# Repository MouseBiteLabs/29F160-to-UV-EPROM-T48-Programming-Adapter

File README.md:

# TSOP NOR Flash Programming Adapter for T48

This is an untested programming adapter for the T48 for programming already-soldered 29F160 chips on my <a href="https://github.com/MouseBiteLabs/ROM-Adapter-Boards/tree/main/29F160%20to%20UV%20EPROM">29F160 to UV EPROM Adapter board.</a> This *should* make it easy to reprogram the one or two flash chips on the adapters without having to desolder anything. I have not tested this yet, so consider this *experimental*. I will, of course, update the repo accordingly if my testing proves successful.

All gerbers and source files can be found in this repo, as this project is fully open source. Please read all instructions associated with this board before assembling.

## Board Characteristics and Order Information

The zipped folder contains all the gerber files for this board. You can generally choose whatever thickness you want, but I usually stick to at least 1.0mm.

You can order this board on OSH Park here: https://oshpark.com/shared_projects/9QicVnyQ

Alternatively, you can use the zipped folder at any board fabricator you like. You may also buy the board from PCBWay using this link (NOT YET AVAILABLE) (disclosure: I receive 10% of the sale value to go towards future PCB orders of my own):

## Required Equipment

- You will need basic tools, like a soldering iron.
- You'll need an extra 2x8 2.54mm female-female IDC ribbon cable, like this one: https://www.digikey.com/short/b1q09p80
  - Alternatively, you can use DuPont breadboard female-female jumpers, like these: https://www.digikey.com/short/vm5d3m4h
- This programming adapter requires the <a href="https://xgecu.myshopify.com/products/100-original-xgecu-adp_f48_ex-1-tsop48-special-adapter-for-nor-flash-only-use-on-t48-tl866-3g-programmer">T48's XGecu TSOP adapter board</a> to be placed on the right socket (P1). This is because it has a proprietary EEPROM (U1) that communicates with the T48.
  - If you want, you can transfer over this EEPROM to *this* adapter board, along with R1 and C1 (a 4.7k resistor and 0.1uF capacitor); or you could simply piggy-back the TSOP adapter on P1, connect the ISP cable from J2 to the TSOP adapter, and keep the TSOP socket unused.

## Supported Boards

P2 accepts the v2.0 version of the 29F160 to UV EPROM adapter boards. It does not support previous revisions.

## How to Assemble and Use the Adapter

### Step 1: Assembly

- You will likely want to populate the right side of each row of pins first with male header pins (2.54mm), which need to have the longer sides sticking down below the board. This will be the rows of pins that go into the T48 programmer. Then, populate the left side of each row of pins with female header pins (2.54mm). This will be where the XGecu TSOP Adapter is housed. 

It's much easier to assemble it in this way, as you can see here:

(Alternatively, you can use only one set of these pins with female socket headers that have longer pins so that you can place it in the T48 *and* connect the XGecu Adapter.)

- P2 and the /BYTE, /RP, and /WE pins (the ones located inside the P2 footprint) are populated with simple female header sockets (2.54mm).

- J1 and J2 are populated with simple male header pins (2.54mm).

- SW1 and SW2 are SPDT switches: https://www.digikey.com/short/zvmm2dj3

- U1, R1, and C1 are discussed below. They are not required for operation, but may be harvested from the XGecu TSOP Adapter.

### Step 2: Connect XGecu TSOP Adapter and 29F160 to UV EPROM Board

With the programming adapter placed in the T48 (check polarity!), place the XGecu TSOP adapter into P1 on the left in the correct orientation. Then, connect one IDC cable from the T48's 16-pin socket to J1 (again, mind the polarity). Connect a second IDC cable from J2 to the XGecu TSOP adapter.

Finally, place the 29F160 to UV EPROM board in the left socket P2.

[TO DO: pic]

### Step 3: Configure the Switches

SW1 and SW2 are for correctly configuring the 29F160 UV EPROM board for programming.

If you are using just one 29F160 chip, place SW2 in the "1x NOR" setting. If you are using two, then place SW2 in the "2x NOR" setting.

When programming a 2x 29F160 board, your ROM files must be in 2MB (16Mbit) chunks. To program the first 29F160 with the first 2MB chunk, place SW1 in the "1ST" setting. To program the second, switch SW1 to the "2ND" setting. If you are only using 1x 29F160, this switch does nothing.

## Bill of Materials (BOM)

As far as the headers (male and female) go, there are plenty of places to get them from at better prices. I personally have drawers full of them, so I didn't need to buy any extra. But if you're looking for exact parts, you can use these. The only parts you may need to buy, if you have a stock of headers and jumper cables ready to go, are the EG1271 switches.

Please note that P1 has two different options, and Option A is a set of 2 separate part numbers (this is the option shown in pictures above in the assembly section with separate male and female headers). P2 has three separate part numbers to populate all of the pins with female sockets while being cost effective.

Also note that in breaking with tradition from my other repositories, I have *Digikey* links listed. This is simply because Mouser did not have an equivalent IDC cable that didn't cost like $10. You can find all the other parts on this list at Mouser as well.

| Reference     | Qty | Value/Part Number | Package                                   | Description                     | Source                                                                           |
| ------------- | --- | ----------------- | ----------------------------------------- | ------------------------------- | -------------------------------------------------------------------------------- |
| Cable (Opt A) | 1   | H3CCH-1606G       | 2x8, 0.1" Spacing                         | IDC Cable                       | [https://www.digikey.com/short/j5rt9349](https://www.digikey.com/short/j5rt9349) |
| Cable (Opt B) | 1   | 1950              | \-                                        | Jumper Wire F-to-F              | [https://www.digikey.com/short/5wr7q7fz](https://www.digikey.com/short/5wr7q7fz) |
| J1, J2        | 2   | 77313-818-16LF    | 2x8, 0.1" Spacing                         | 16 Position Header Pins, Male   | [https://www.digikey.com/short/13fhc19n](https://www.digikey.com/short/13fhc19n) |
| SW1, SW2      | 2   | EG1271            | 2x3 Pins                                  | SPDT Slide Switch               | [https://www.digikey.com/short/vj8nm90f](https://www.digikey.com/short/vj8nm90f) |
| P1 (Opt A)    | 2   | PPPC201LFBN-RC    | 20 Pins, 0.1" Spacing                     | 20 Position Header Pins, Female | [https://www.digikey.com/short/7rdtqfvp](https://www.digikey.com/short/7rdtqfvp) |
|               | 2   | PRPC020SAAN-RC    | 20 Pins, 0.1" Spacing                     | 20 Position Header Pins, Male   | [https://www.digikey.com/short/zpzj5p9h](https://www.digikey.com/short/zpzj5p9h) |
| P1 (Opt B)    | 4   | SSQ-110-03-G-S    | 10 Pins, 0.1" Spacing, 0.394" Post Length | 10 Position Header Pins, Female | [https://www.digikey.com/short/rvwzhn13](https://www.digikey.com/short/rvwzhn13) |
| P2            | 2   | PPPC201LFBN-RC    | 20 Pins, 0.1" Spacing                     | 20 Position Header Pins, Female | [https://www.digikey.com/short/7rdtqfvp](https://www.digikey.com/short/7rdtqfvp) |
|               | 1   | PPPC021LFBN-RC    | 2 Pins, 0.1" Spacing                      | 2 Position Header Pins, Female  | [https://www.digikey.com/short/bd5t98qm](https://www.digikey.com/short/bd5t98qm) |
|               | 1   | PPPC031LFBN-RC    | 3 Pins, 0.1" Spacing                      | 3 Position Header Pins, Female  | [https://www.digikey.com/short/p04ft8t8](https://www.digikey.com/short/p04ft8t8) |

## What's with U1, R1, and C1?

On the XGecu TSOP Programming Adapter, these 3 components are included. This is a proprietary EEPROM for communicating with the T48. I believe this is a form of copy protection. If you wish, you can transfer these components over to this board instead - this would remove the need of placing the XGecu adapter into P1. *(Maybe a clever person could reverse engineer the EEPROM by sniffing pins 5 and 6, which are the only two pins used on this chip)*

## What's with the P37/VCC and P29/GND/P18 Pins?

This is basically for helping me troubleshoot if I run into problems. One of the things I'm unsure of is if the T48 will throw an error if it detects the larger-than-normal load due to the extra circuitry on my TSOP adapter boards. 

Pin 37 on the T48 is connected to the VCC pin of the TSOP chip, but it is not directly connected to VCC itself, which is pin 14 of J1/J2. The jumper is there in case the TSOP board current limits the programmer with the extra circuitry on it. Though, that might cause other problems, so it is not hard-wired. Pin 18 and pin 29 are a similar case for VSS.

You can ignore these pins (unless I update the repo further to address them).

## Revision History

### v1.1 - Prototype II

- Disconnected pin 18 and pin 29 on P1 from VSS and connect to the proper pins on P2 instead
- Renamed board to be more general
- Added more pins for ZIF socket access

### v1.0 - Prototype

## License

<br />This work is licensed under a <a rel="license" href="http://creativecommons.org/licenses/by-sa/4.0/">Creative Commons Attribution-ShareAlike 4.0 International License</a>. You are able to copy and redistribute the material in any medium or format, as well as remix, transform, or build upon the material for any purpose (even commercial) - but you **must** give appropriate credit, provide a link to the license, and indicate if any changes were made.

©MouseBiteLabs 2025

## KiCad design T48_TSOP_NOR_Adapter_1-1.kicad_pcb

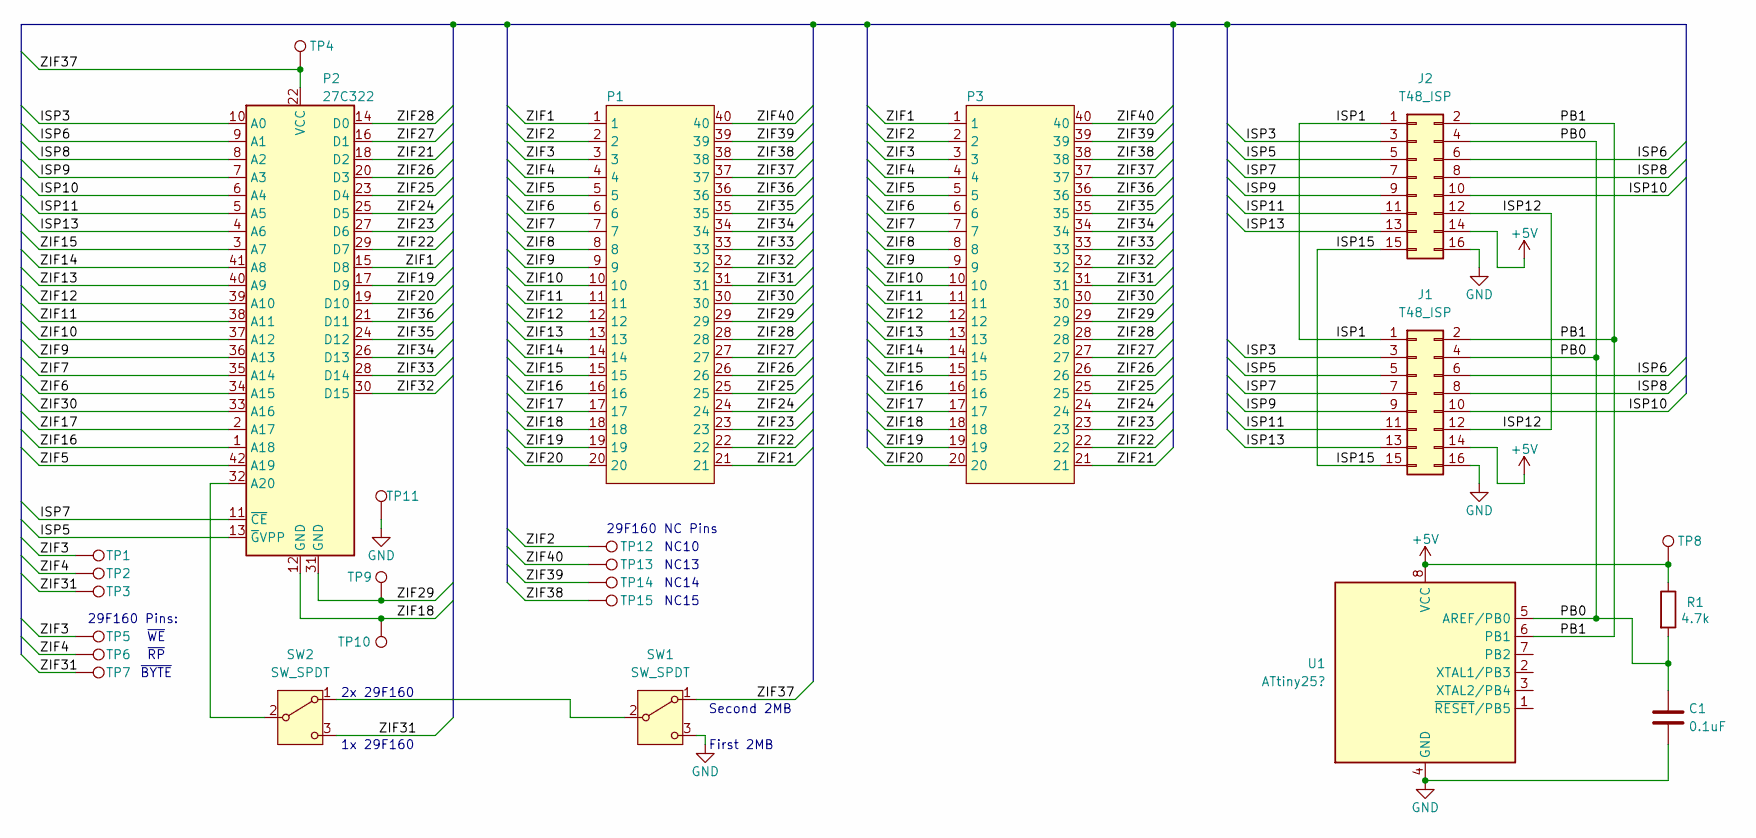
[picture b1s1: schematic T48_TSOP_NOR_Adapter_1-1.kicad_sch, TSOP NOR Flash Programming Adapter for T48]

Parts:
C1: 0.1uF; C_0603_1608Metric_Boxed
J1, J2: T48_ISP; PinHeader_2x08_P2.54mm_Vertical
P1, P3: T48_ZIF
P2: 27C322; DIP-42_W15.24mm
R1: 4.7k; R_0603_1608Metric_Boxed
SW1, SW2: SW_SPDT; SW_E-Switch_EG1271_SPDT
TP1, TP2, TP3, TP4, TP5, TP6, TP7, TP8, TP9, TP10, TP11, TP12, TP13, TP14, TP15: TPB1,27; TestPoint_THTPad_D1.5mm_Drill0.7mm
U1: ATtiny25?; SOIC-8_3.9x4.9mm_P1.27mm

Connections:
+5V: J1.14, J2.14, R1.1, TP8.1, U1.8 (VCC)
/ISP1: J1.1, J2.1
/ISP3: J1.3, J2.3, P2.10 (A0)
/ISP5: J1.5, J2.5, P2.13 (~GVPP)
/ISP6: J1.6, J2.6, P2.9 (A1)
/ISP7: J1.7, J2.7, P2.11 (~CE)
/ISP8: J1.8, J2.8, P2.8 (A2)
/ISP9: J1.9, J2.9, P2.7 (A3)
/ISP10: J1.10, J2.10, P2.6 (A4)
/ISP11: J1.11, J2.11, P2.5 (A5)
/ISP12: J1.12, J2.12
/ISP13: J1.13, J2.13, P2.4 (A6)
/ISP15: J1.15, J2.15
/PB0: C1.1, J1.4, J2.4, R1.2, U1.5 (AREF/PB0)
/PB1: J1.2, J2.2, U1.6 (PB1)
/ZIF1: P1.1, P2.15 (D8), P3.1
/ZIF2: P1.2, P3.2, TP12.1
/ZIF3: P1.3, P3.3, TP1.1, TP5.1
/ZIF4: P1.4, P3.4, TP2.1, TP6.1
/ZIF5: P1.5, P2.42 (A19), P3.5
/ZIF6: P1.6, P2.34 (A15), P3.6
/ZIF7: P1.7, P2.35 (A14), P3.7
/ZIF8: P1.8, P3.8
/ZIF9: P1.9, P2.36 (A13), P3.9
/ZIF10: P1.10, P2.37 (A12), P3.10
/ZIF11: P1.11, P2.38 (A11), P3.11
/ZIF12: P1.12, P2.39 (A10), P3.12
/ZIF13: P1.13, P2.40 (A9), P3.13
/ZIF14: P1.14, P2.41 (A8), P3.14
/ZIF15: P1.15, P2.3 (A7), P3.15
/ZIF16: P1.16, P2.1 (A18), P3.16
/ZIF17: P1.17, P2.2 (A17), P3.17
/ZIF18: P1.18, P2.12 (GND), P3.18, TP10.1
/ZIF19: P1.19, P2.17 (D9), P3.19
/ZIF20: P1.20, P2.19 (D10), P3.20
/ZIF21: P1.21, P2.18 (D2), P3.21
/ZIF22: P1.22, P2.29 (D7), P3.22
/ZIF23: P1.23, P2.27 (D6), P3.23
/ZIF24: P1.24, P2.25 (D5), P3.24
/ZIF25: P1.25, P2.23 (D4), P3.25
/ZIF26: P1.26, P2.20 (D3), P3.26
/ZIF27: P1.27, P2.16 (D1), P3.27
/ZIF28: P1.28, P2.14 (D0), P3.28
/ZIF29: P1.29, P2.31 (GND), P3.29, TP9.1
/ZIF30: P1.30, P2.33 (A16), P3.30
/ZIF31: P1.31, P3.31, SW2.3 (C), TP3.1, TP7.1
/ZIF32: P1.32, P2.30 (D15), P3.32
/ZIF33: P1.33, P2.28 (D14), P3.33
/ZIF34: P1.34, P2.26 (D13), P3.34
/ZIF35: P1.35, P2.24 (D12), P3.35
/ZIF36: P1.36, P2.21 (D11), P3.36
/ZIF37: P1.37, P2.22 (VCC), P3.37, SW1.1 (A), TP4.1
/ZIF38: P1.38, P3.38, TP15.1
/ZIF39: P1.39, P3.39, TP14.1
/ZIF40: P1.40, P3.40, TP13.1
GND: C1.2, J1.16, J2.16, SW1.3 (C), TP11.1, U1.4 (GND)
unnamed: P2.32 (A20), SW2.2 (B)
unnamed: SW1.2 (B), SW2.1 (A)

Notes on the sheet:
~{WE}
NC15
NC14
29F160 NC Pins
1x 29F160
NC10
First 2MB
2x 29F160
~{RP}
29F160 Pins:
Second 2MB
~{BYTE}
NC13

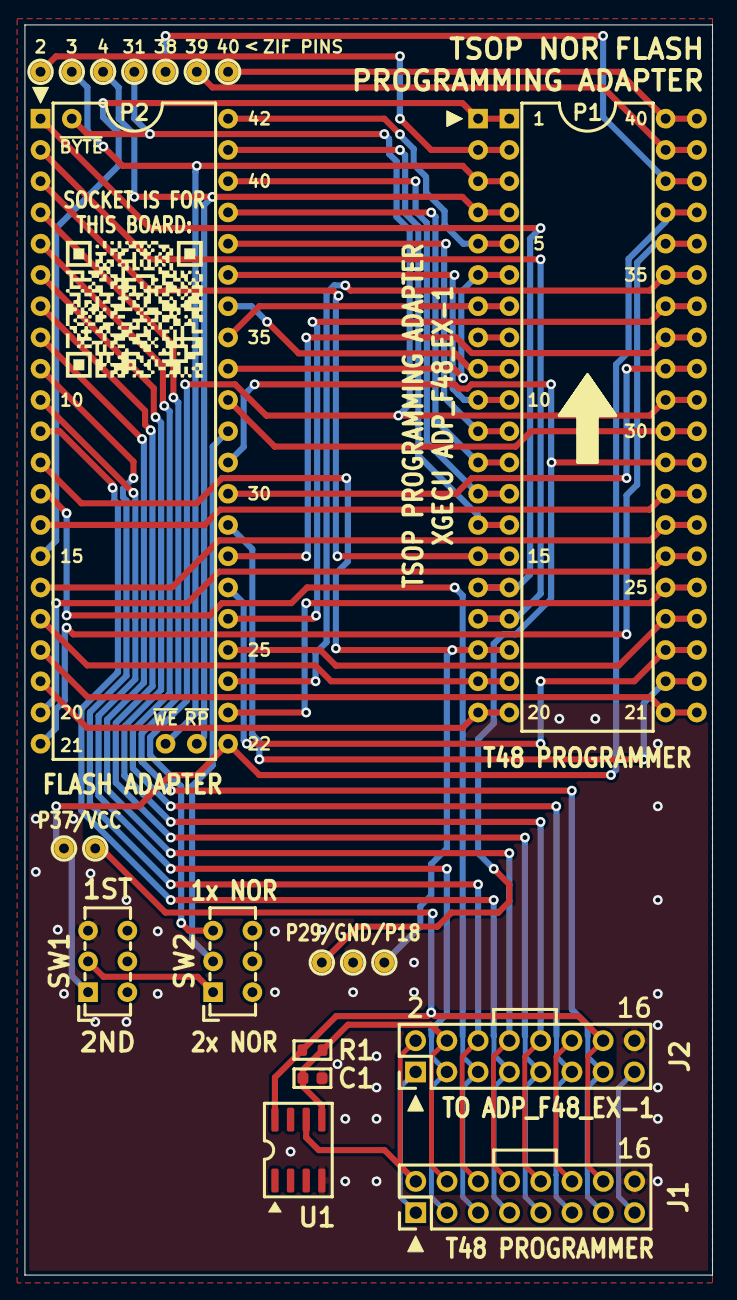
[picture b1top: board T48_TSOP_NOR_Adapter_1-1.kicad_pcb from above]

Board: 2 copper layers, 55.9 x 101.6 mm, 25 parts (0 on the bottom side), 58 nets.
